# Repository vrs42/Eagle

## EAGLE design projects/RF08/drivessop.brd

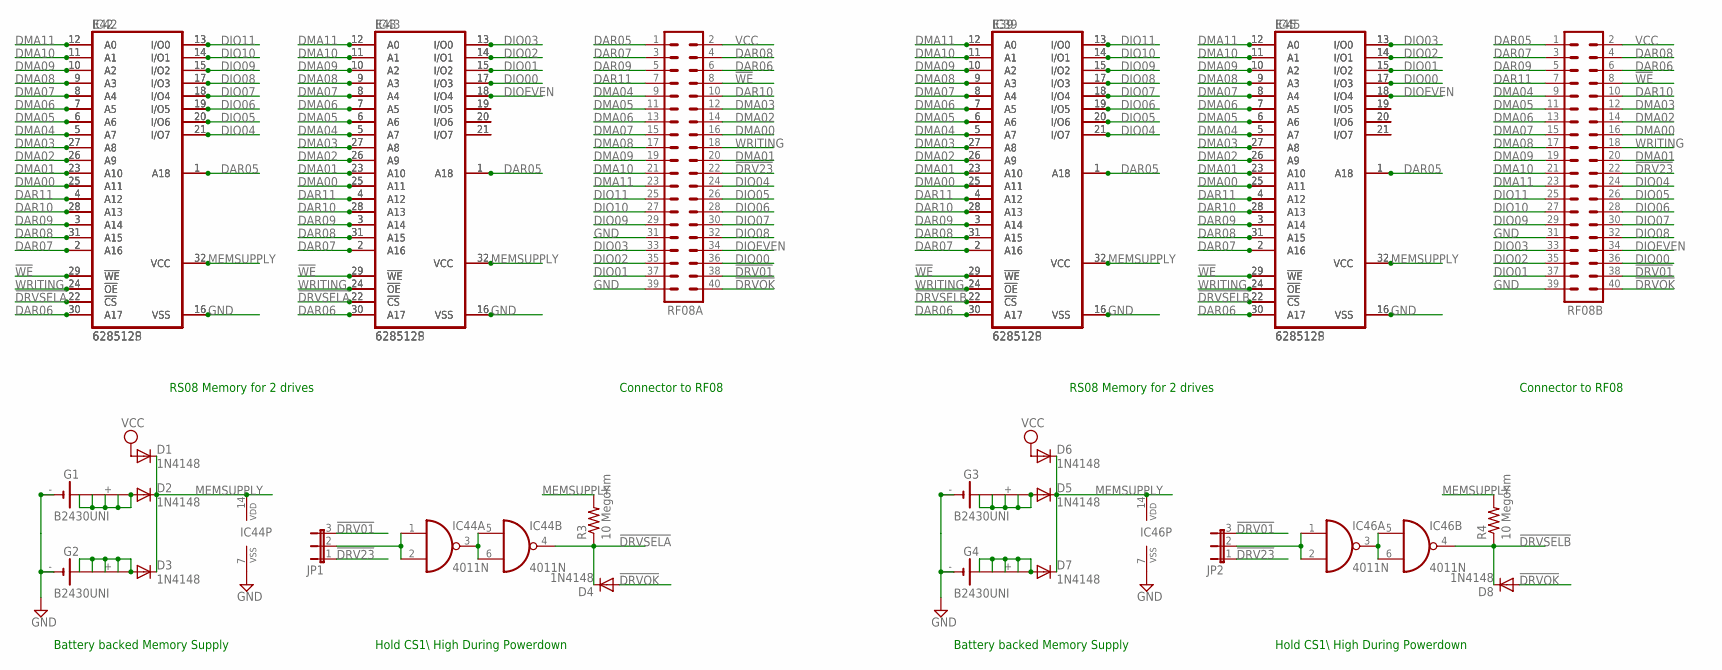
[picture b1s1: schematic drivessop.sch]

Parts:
D1, D2, D3, D4, D5, D6, D7, D8: 1N4148; DO35-10
E39, E42, E43, E45: 628512S; S032L
G1, G2, G3, G4: B2430UNI
IC39, IC42, IC43, IC45: 628512P; DIL32
IC44, IC46: 4011N; DIL14
JP1, JP2: JP2E; JP2
R3, R4: 10 Megohm; 0207/10
RF08A, RF08B: MA20-2

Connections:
!DRV01: JP1.3, JP2.3, RF08A.38, RF08B.38
!DRV23: JP1.1, JP2.1, RF08A.22, RF08B.22
!DRVOK: D4.A, D8.A, RF08A.40, RF08B.40
!DRVSELA: D4.C, E42.22 (!CS), E43.22 (!CS), IC42.22 (!CS), IC43.22 (!CS), IC44.4 (O), R3.1
!DRVSELB: D8.C, E39.22 (!CS), E45.22 (!CS), IC39.22 (!CS), IC45.22 (!CS), IC46.4 (O), R4.1
!WE: E39.29 (!WE), E42.29 (!WE), E43.29 (!WE), E45.29 (!WE), IC39.29 (!WE), IC42.29 (!WE), IC43.29 (!WE), IC45.29 (!WE), RF08A.8, RF08B.8
DAR05: E39.1 (A18), E42.1 (A18), E43.1 (A18), E45.1 (A18), IC39.1 (A18), IC42.1 (A18), IC43.1 (A18), IC45.1 (A18), RF08A.1, RF08B.1
DAR06: E39.30 (A17), E42.30 (A17), E43.30 (A17), E45.30 (A17), IC39.30 (A17), IC42.30 (A17), IC43.30 (A17), IC45.30 (A17), RF08A.6, RF08B.6
DAR07: E39.2 (A16), E42.2 (A16), E43.2 (A16), E45.2 (A16), IC39.2 (A16), IC42.2 (A16), IC43.2 (A16), IC45.2 (A16), RF08A.3, RF08B.3
DAR08: E39.31 (A15), E42.31 (A15), E43.31 (A15), E45.31 (A15), IC39.31 (A15), IC42.31 (A15), IC43.31 (A15), IC45.31 (A15), RF08A.4, RF08B.4
DAR09: E39.3 (A14), E42.3 (A14), E43.3 (A14), E45.3 (A14), IC39.3 (A14), IC42.3 (A14), IC43.3 (A14), IC45.3 (A14), RF08A.5, RF08B.5
DAR10: E39.28 (A13), E42.28 (A13), E43.28 (A13), E45.28 (A13), IC39.28 (A13), IC42.28 (A13), IC43.28 (A13), IC45.28 (A13), RF08A.10, RF08B.10
DAR11: E39.4 (A12), E42.4 (A12), E43.4 (A12), E45.4 (A12), IC39.4 (A12), IC42.4 (A12), IC43.4 (A12), IC45.4 (A12), RF08A.7, RF08B.7
DIO00: E43.17 (I/O3), E45.17 (I/O3), IC43.17 (I/O3), IC45.17 (I/O3), RF08A.36, RF08B.36
DIO01: E43.15 (I/O2), E45.15 (I/O2), IC43.15 (I/O2), IC45.15 (I/O2), RF08A.37, RF08B.37
DIO02: E43.14 (I/O1), E45.14 (I/O1), IC43.14 (I/O1), IC45.14 (I/O1), RF08A.35, RF08B.35
DIO03: E43.13 (I/O0), E45.13 (I/O0), IC43.13 (I/O0), IC45.13 (I/O0), RF08A.33, RF08B.33
DIO04: E39.21 (I/O7), E42.21 (I/O7), IC39.21 (I/O7), IC42.21 (I/O7), RF08A.24, RF08B.24
DIO05: E39.20 (I/O6), E42.20 (I/O6), IC39.20 (I/O6), IC42.20 (I/O6), RF08A.26, RF08B.26
DIO06: E39.19 (I/O5), E42.19 (I/O5), IC39.19 (I/O5), IC42.19 (I/O5), RF08A.28, RF08B.28
DIO07: E39.18 (I/O4), E42.18 (I/O4), IC39.18 (I/O4), IC42.18 (I/O4), RF08A.30, RF08B.30
DIO08: E39.17 (I/O3), E42.17 (I/O3), IC39.17 (I/O3), IC42.17 (I/O3), RF08A.32, RF08B.32
DIO09: E39.15 (I/O2), E42.15 (I/O2), IC39.15 (I/O2), IC42.15 (I/O2), RF08A.29, RF08B.29
DIO10: E39.14 (I/O1), E42.14 (I/O1), IC39.14 (I/O1), IC42.14 (I/O1), RF08A.27, RF08B.27
DIO11: E39.13 (I/O0), E42.13 (I/O0), IC39.13 (I/O0), IC42.13 (I/O0), RF08A.25, RF08B.25
DIOEVEN: E43.18 (I/O4), E45.18 (I/O4), IC43.18 (I/O4), IC45.18 (I/O4), RF08A.34, RF08B.34
DMA00: E39.25 (A11), E42.25 (A11), E43.25 (A11), E45.25 (A11), IC39.25 (A11), IC42.25 (A11), IC43.25 (A11), IC45.25 (A11), RF08A.16, RF08B.16
DMA01: E39.23 (A10), E42.23 (A10), E43.23 (A10), E45.23 (A10), IC39.23 (A10), IC42.23 (A10), IC43.23 (A10), IC45.23 (A10), RF08A.20, RF08B.20
DMA02: E39.26 (A9), E42.26 (A9), E43.26 (A9), E45.26 (A9), IC39.26 (A9), IC42.26 (A9), IC43.26 (A9), IC45.26 (A9), RF08A.14, RF08B.14
DMA03: E39.27 (A8), E42.27 (A8), E43.27 (A8), E45.27 (A8), IC39.27 (A8), IC42.27 (A8), IC43.27 (A8), IC45.27 (A8), RF08A.12, RF08B.12
DMA04: E39.5 (A7), E42.5 (A7), E43.5 (A7), E45.5 (A7), IC39.5 (A7), IC42.5 (A7), IC43.5 (A7), IC45.5 (A7), RF08A.9, RF08B.9
DMA05: E39.6 (A6), E42.6 (A6), E43.6 (A6), E45.6 (A6), IC39.6 (A6), IC42.6 (A6), IC43.6 (A6), IC45.6 (A6), RF08A.11, RF08B.11
DMA06: E39.7 (A5), E42.7 (A5), E43.7 (A5), E45.7 (A5), IC39.7 (A5), IC42.7 (A5), IC43.7 (A5), IC45.7 (A5), RF08A.13, RF08B.13
DMA07: E39.8 (A4), E42.8 (A4), E43.8 (A4), E45.8 (A4), IC39.8 (A4), IC42.8 (A4), IC43.8 (A4), IC45.8 (A4), RF08A.15, RF08B.15
DMA08: E39.9 (A3), E42.9 (A3), E43.9 (A3), E45.9 (A3), IC39.9 (A3), IC42.9 (A3), IC43.9 (A3), IC45.9 (A3), RF08A.17, RF08B.17
DMA09: E39.10 (A2), E42.10 (A2), E43.10 (A2), E45.10 (A2), IC39.10 (A2), IC42.10 (A2), IC43.10 (A2), IC45.10 (A2), RF08A.19, RF08B.19
DMA10: E39.11 (A1), E42.11 (A1), E43.11 (A1), E45.11 (A1), IC39.11 (A1), IC42.11 (A1), IC43.11 (A1), IC45.11 (A1), RF08A.21, RF08B.21
DMA11: E39.12 (A0), E42.12 (A0), E43.12 (A0), E45.12 (A0), IC39.12 (A0), IC42.12 (A0), IC43.12 (A0), IC45.12 (A0), RF08A.23, RF08B.23
GND: E39.16 (VSS), E42.16 (VSS), E43.16 (VSS), E45.16 (VSS), G1.-, G1.-@1 (-), G2.-, G2.-@1 (-), G3.-, G3.-@1 (-), G4.-, G4.-@1 (-), IC39.16 (VSS), IC42.16 (VSS), IC43.16 (VSS), IC44.7 (VSS), IC45.16 (VSS), IC46.7 (VSS), RF08A.31, RF08A.39, RF08B.31, RF08B.39
MEMSUPPLY: D1.C, D2.C, D3.C, D5.C, D6.C, D7.C, E39.32 (VCC), E42.32 (VCC), E43.32 (VCC), E45.32 (VCC), IC39.32 (VCC), IC42.32 (VCC), IC43.32 (VCC), IC44.14 (VDD), IC45.32 (VCC), IC46.14 (VDD), R3.2, R4.2
unnamed: E43.19 (I/O5), IC43.19 (I/O5)
unnamed: E43.20 (I/O6), IC43.20 (I/O6)
unnamed: E43.21 (I/O7), IC43.21 (I/O7)
unnamed: E45.19 (I/O5), IC45.19 (I/O5)
unnamed: E45.20 (I/O6), IC45.20 (I/O6)
unnamed: E45.21 (I/O7), IC45.21 (I/O7)
unnamed: IC44.3 (O), IC44.5 (I0), IC44.6 (I1)
unnamed: IC44.1 (I0), IC44.2 (I1), JP1.2
unnamed: D7.A, G4.+, G4.+@1 (+), G4.+@2 (+), G4.+@3 (+), G4.+@4 (+)
unnamed: IC46.3 (O), IC46.5 (I0), IC46.6 (I1)
unnamed: IC46.1 (I0), IC46.2 (I1), JP2.2
unnamed: D5.A, G3.+, G3.+@1 (+), G3.+@2 (+), G3.+@3 (+), G3.+@4 (+)
unnamed: D3.A, G2.+, G2.+@1 (+), G2.+@2 (+), G2.+@3 (+), G2.+@4 (+)
unnamed: D2.A, G1.+, G1.+@1 (+), G1.+@2 (+), G1.+@3 (+), G1.+@4 (+)
VCC: D1.A, D6.A, RF08A.2, RF08B.2
WRITING: E39.24 (!OE), E42.24 (!OE), E43.24 (!OE), E45.24 (!OE), IC39.24 (!OE), IC42.24 (!OE), IC43.24 (!OE), IC45.24 (!OE), RF08A.18, RF08B.18

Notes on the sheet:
Hold CS1\\ High During Powerdown
Battery backed Memory Supply
RS08 Memory for 2 drives
Connector to RF08

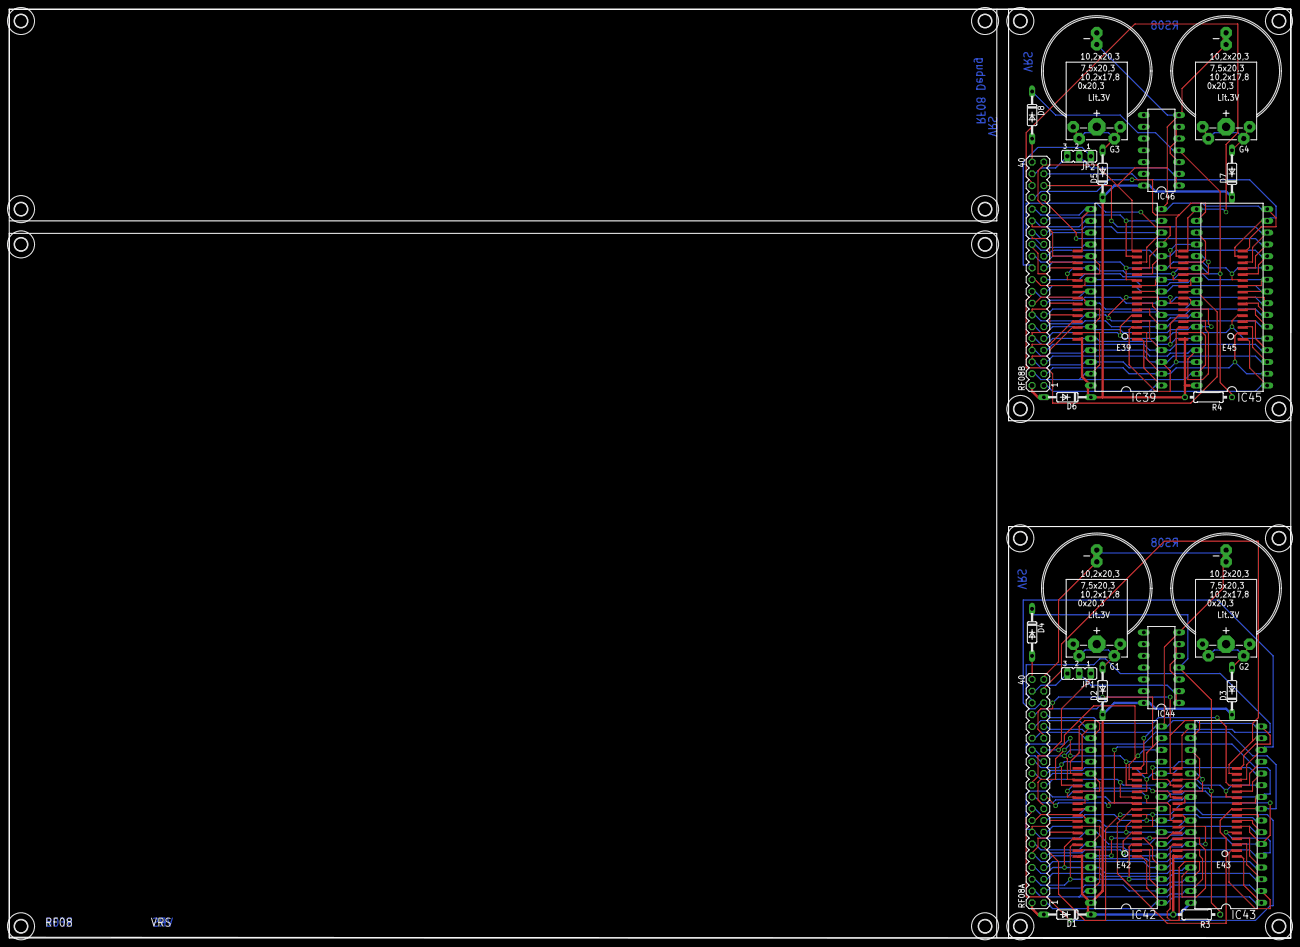
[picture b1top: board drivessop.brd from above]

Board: 2 copper layers, 276.9 x 200.7 mm, 45 parts (0 on the bottom side), 56 nets.

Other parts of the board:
U$1, U$2, U$3, U$4, U$5, U$6, U$7, U$8, U$9, U$10, U$11, U$12, U$13, U$14, U$16, U$17: 2,8
U$18: SIERRA-PROTO

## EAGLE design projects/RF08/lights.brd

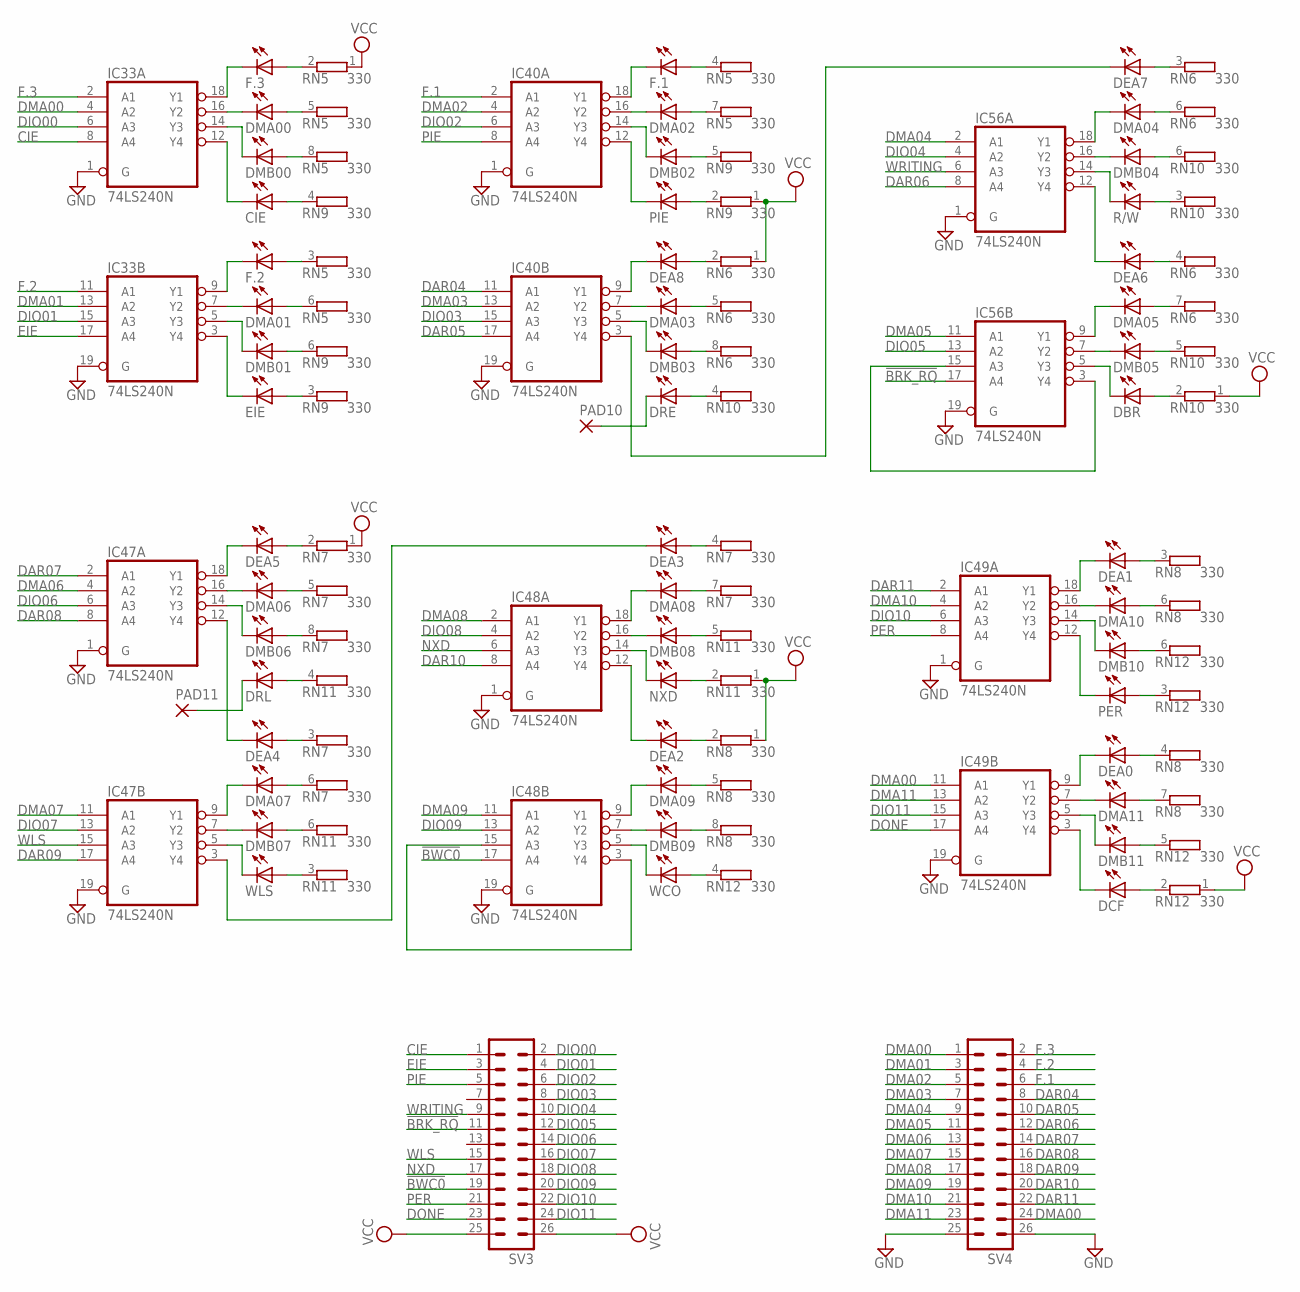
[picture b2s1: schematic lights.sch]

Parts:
CIE: LED5MM
DBR: LED5MM
DCF: LED5MM
DEA0, DEA1, DEA2, DEA3, DEA4, DEA5, DEA6, DEA7, DEA8: LED5MM
DMA00, DMA01, DMA02, DMA03, DMA04, DMA05, DMA06, DMA07, DMA08, DMA09, DMA10, DMA11: LED5MM
DMB00, DMB01, DMB02, DMB03, DMB04, DMB05, DMB06, DMB07, DMB08, DMB09, DMB10, DMB11: LED5MM
DRE: LED5MM
DRL: LED5MM
EIE: LED5MM
F.1, F.2, F.3: LED5MM
IC33, IC40, IC47, IC48, IC49, IC56: 74LS240N; DIL20
NXD: LED5MM
PAD10, PAD11: 1,6/0,8
PER: LED5MM
PIE: LED5MM
R/W: LED5MM
RN5, RN6, RN7, RN8: 330; SIL8
RN9, RN10, RN11, RN12: 330; SIL6
SV3, SV4: MA13-2
WCO: LED5MM
WLS: LED5MM

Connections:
!BRK_RQ: IC56.17 (A4), SV3.11
!BWC0: IC48.17 (A4), SV3.19
CIE: IC33.8 (A4), SV3.1
DAR04: IC40.11 (A1), SV4.8
DAR05: IC40.17 (A4), SV4.10
DAR06: IC56.8 (A4), SV4.12
DAR07: IC47.2 (A1), SV4.14
DAR08: IC47.8 (A4), SV4.16
DAR09: IC47.17 (A4), SV4.18
DAR10: IC48.8 (A4), SV4.20
DAR11: IC49.2 (A1), SV4.22
DIO00: IC33.6 (A3), SV3.2
DIO01: IC33.15 (A3), SV3.4
DIO02: IC40.6 (A3), SV3.6
DIO03: IC40.15 (A3), SV3.8
DIO04: IC56.4 (A2), SV3.10
DIO05: IC56.13 (A2), SV3.12
DIO06: IC47.6 (A3), SV3.14
DIO07: IC47.13 (A2), SV3.16
DIO08: IC48.4 (A2), SV3.18
DIO09: IC48.13 (A2), SV3.20
DIO10: IC49.6 (A3), SV3.22
DIO11: IC49.15 (A3), SV3.24
DMA00: IC33.4 (A2), IC49.11 (A1), SV4.1, SV4.24
DMA01: IC33.13 (A2), SV4.3
DMA02: IC40.4 (A2), SV4.5
DMA03: IC40.13 (A2), SV4.7
DMA04: IC56.2 (A1), SV4.9
DMA05: IC56.11 (A1), SV4.11
DMA06: IC47.4 (A2), SV4.13
DMA07: IC47.11 (A1), SV4.15
DMA08: IC48.2 (A1), SV4.17
DMA09: IC48.11 (A1), SV4.19
DMA10: IC49.4 (A2), SV4.21
DMA11: IC49.13 (A2), SV4.23
DONE: IC49.17 (A4), SV3.23
EIE: IC33.17 (A4), SV3.3
F.1: IC40.2 (A1), SV4.6
F.2: IC33.11 (A1), SV4.4
F.3: IC33.2 (A1), SV4.2
GND: IC33.1 (G), IC33.10 (GND), IC33.19 (G), IC40.1 (G), IC40.10 (GND), IC40.19 (G), IC47.1 (G), IC47.10 (GND), IC47.19 (G), IC48.1 (G), IC48.10 (GND), IC48.19 (G), IC49.1 (G), IC49.10 (GND), IC49.19 (G), IC56.1 (G), IC56.10 (GND), IC56.19 (G), SV4.25, SV4.26
unnamed: F.3.A, RN5.2
unnamed: F.2.A, RN5.3 (2)
unnamed: F.1.A, RN5.4 (2)
unnamed: DEA8.A, RN6.2
unnamed: DEA2.A, RN8.2
unnamed: DEA1.A, RN8.3 (2)
unnamed: DEA5.A, RN7.2
unnamed: DEA4.A, RN7.3 (2)
unnamed: DEA3.A, RN7.4 (2)
unnamed: DEA0.A, RN8.4 (2)
unnamed: DMA09.A, RN8.5 (2)
unnamed: DMA10.A, RN8.6 (2)
unnamed: DMA00.A, RN5.5 (2)
unnamed: DMA01.A, RN5.6 (2)
unnamed: DMA02.A, RN5.7 (2)
unnamed: DEA7.A, RN6.3 (2)
unnamed: DEA6.A, RN6.4 (2)
unnamed: DMA03.A, RN6.5 (2)
unnamed: DMA07.A, RN7.6 (2)
unnamed: DMA06.A, RN7.5 (2)
unnamed: DMA08.A, RN7.7 (2)
unnamed: DMA11.A, RN8.7 (2)
unnamed: DMB09.A, RN8.8 (2)
unnamed: DMB10.A, RN12.6 (2)
unnamed: PIE.A, RN9.2
unnamed: EIE.A, RN9.3 (2)
unnamed: CIE.A, RN9.4 (2)
unnamed: DMA04.A, RN6.6 (2)
unnamed: DMA05.A, RN6.7 (2)
unnamed: DMB03.A, RN6.8 (2)
unnamed: DMB06.A, RN7.8 (2)
unnamed: DMB07.A, RN11.6 (2)
unnamed: DMB08.A, RN11.5 (2)
unnamed: DMB11.A, RN12.5 (2)
unnamed: RN12.4 (2), WCO.A
unnamed: PER.A, RN12.3 (2)
unnamed: DMB02.A, RN9.5 (2)
unnamed: DMB01.A, RN9.6 (2)
unnamed: DMB00.A, RN5.8 (2)
unnamed: DRE.A, RN10.4 (2)
unnamed: R/W.A, RN10.3 (2)
unnamed: DBR.A, RN10.2
unnamed: DRL.A, RN11.4 (2)
unnamed: RN11.3 (2), WLS.A
unnamed: NXD.A, RN11.2
unnamed: DCF.A, RN12.2
unnamed: DMA09.K (C), IC48.9 (Y1)
unnamed: DMB09.K (C), IC48.7 (Y2)
unnamed: F.3.K (C), IC33.18 (Y1)
unnamed: DMA00.K (C), IC33.16 (Y2)
unnamed: CIE.K (C), IC33.12 (Y4)
unnamed: DMB00.K (C), IC33.14 (Y3)
unnamed: DMA01.K (C), IC33.7 (Y2)
unnamed: F.2.K (C), IC33.9 (Y1)
unnamed: DMB01.K (C), IC33.5 (Y3)
unnamed: EIE.K (C), IC33.3 (Y4)
unnamed: F.1.K (C), IC40.18 (Y1)
unnamed: DMA02.K (C), IC40.16 (Y2)
unnamed: DMB02.K (C), IC40.14 (Y3)
unnamed: IC40.12 (Y4), PIE.K (C)
unnamed: DMB03.K (C), IC40.5 (Y3)
unnamed: DMA03.K (C), IC40.7 (Y2)
unnamed: DEA8.K (C), IC40.9 (Y1)
unnamed: DEA7.K (C), IC40.3 (Y4)
unnamed: DMA04.K (C), IC56.18 (Y1)
unnamed: DMB04.K (C), IC56.16 (Y2)
unnamed: IC56.14 (Y3), R/W.K (C)
unnamed: DMB05.K (C), IC56.7 (Y2)
unnamed: DEA6.K (C), IC56.12 (Y4)
unnamed: DBR.K (C), IC56.5 (Y3)
unnamed: DMA06.K (C), IC47.16 (Y2)
unnamed: DEA4.K (C), IC47.12 (Y4)
unnamed: DMB07.K (C), IC47.7 (Y2)
unnamed: DEA5.K (C), IC47.18 (Y1)
unnamed: DMA07.K (C), IC47.9 (Y1)
unnamed: IC47.5 (Y3), WLS.K (C)
unnamed: DMB06.K (C), IC47.14 (Y3)
unnamed: DEA3.K (C), IC47.3 (Y4)
unnamed: DMA08.K (C), IC48.18 (Y1)
unnamed: DMB08.K (C), IC48.16 (Y2)
unnamed: IC48.14 (Y3), NXD.K (C)
unnamed: IC48.5 (Y3), WCO.K (C)
unnamed: IC49.12 (Y4), PER.K (C)
unnamed: DMB10.K (C), IC49.14 (Y3)
unnamed: DEA2.K (C), IC48.12 (Y4)
unnamed: DMA10.K (C), IC49.16 (Y2)
unnamed: DEA1.K (C), IC49.18 (Y1)
unnamed: IC48.3 (Y4), IC48.15 (A3)
unnamed: DMA11.K (C), IC49.7 (Y2)
unnamed: DEA0.K (C), IC49.9 (Y1)
unnamed: DMB11.K (C), IC49.5 (Y3)
unnamed: DCF.K (C), IC49.3 (Y4)
unnamed: DRE.K (C), PAD10.1
unnamed: DRL.K (C), PAD11.1
unnamed: DMA05.K (C), IC56.9 (Y1)
unnamed: DMB04.A, RN10.6 (2)
unnamed: DMB05.A, RN10.5 (2)
unnamed: IC56.3 (Y4), IC56.15 (A3)
NXD: IC48.6 (A3), SV3.17
PER: IC49.8 (A4), SV3.21
PIE: IC40.8 (A4), SV3.5
VCC: IC33.20 (VCC), IC40.20 (VCC), IC47.20 (VCC), IC48.20 (VCC), IC49.20 (VCC), IC56.20 (VCC), RN5.1, RN6.1, RN7.1, RN8.1, RN9.1, RN10.1, RN11.1, RN12.1, SV3.25, SV3.26
WLS: IC47.15 (A3), SV3.15
WRITING: IC56.6 (A3), SV3.9

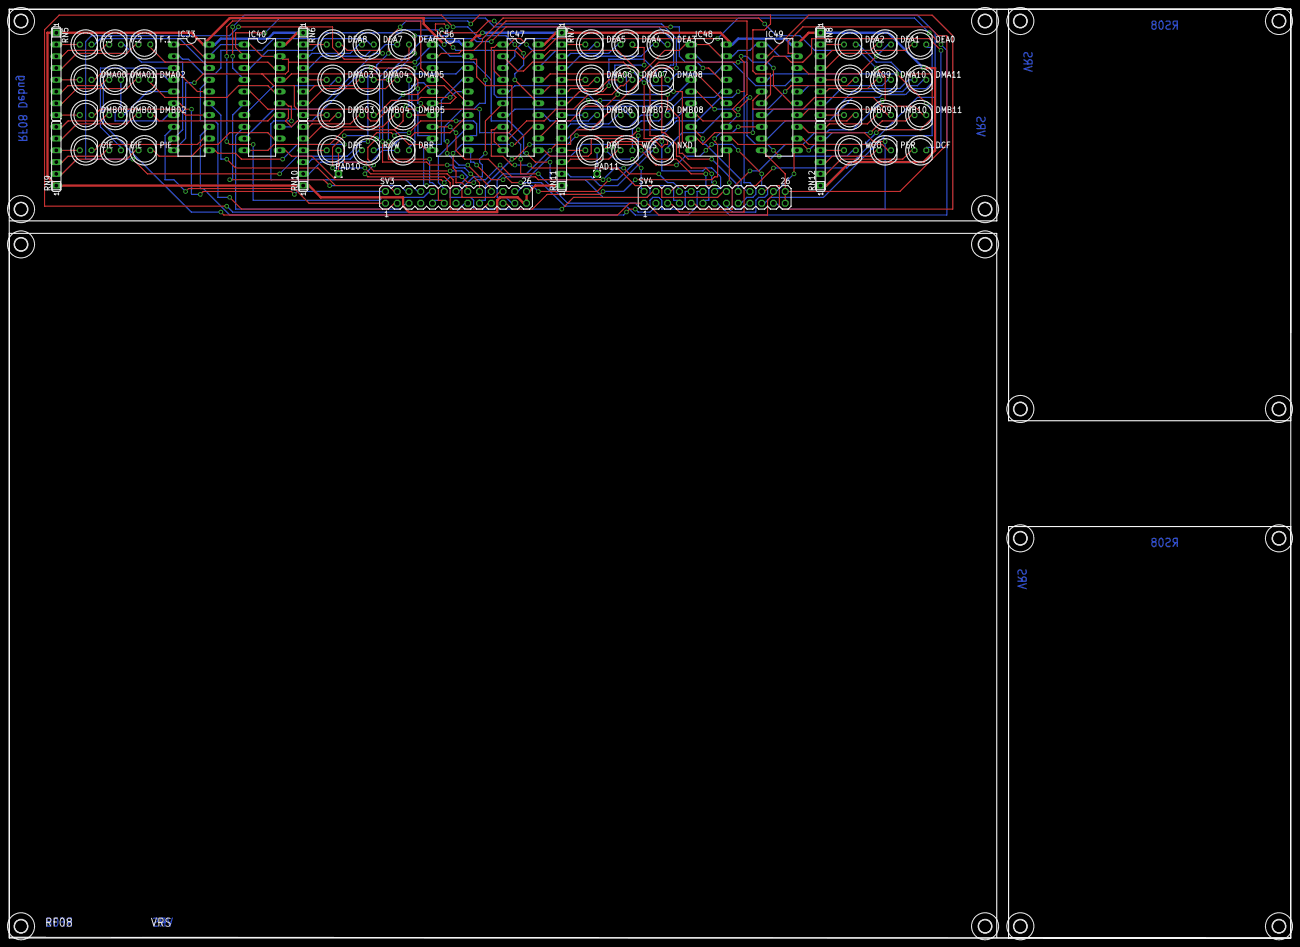
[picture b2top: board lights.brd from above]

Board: 2 copper layers, 276.9 x 200.7 mm, 83 parts (0 on the bottom side), 145 nets.

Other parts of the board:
U$1, U$2, U$3, U$4, U$5, U$6, U$7, U$8, U$9, U$10, U$11, U$12, U$13, U$14, U$16, U$17: 2,8
U$18: SIERRA-PROTO

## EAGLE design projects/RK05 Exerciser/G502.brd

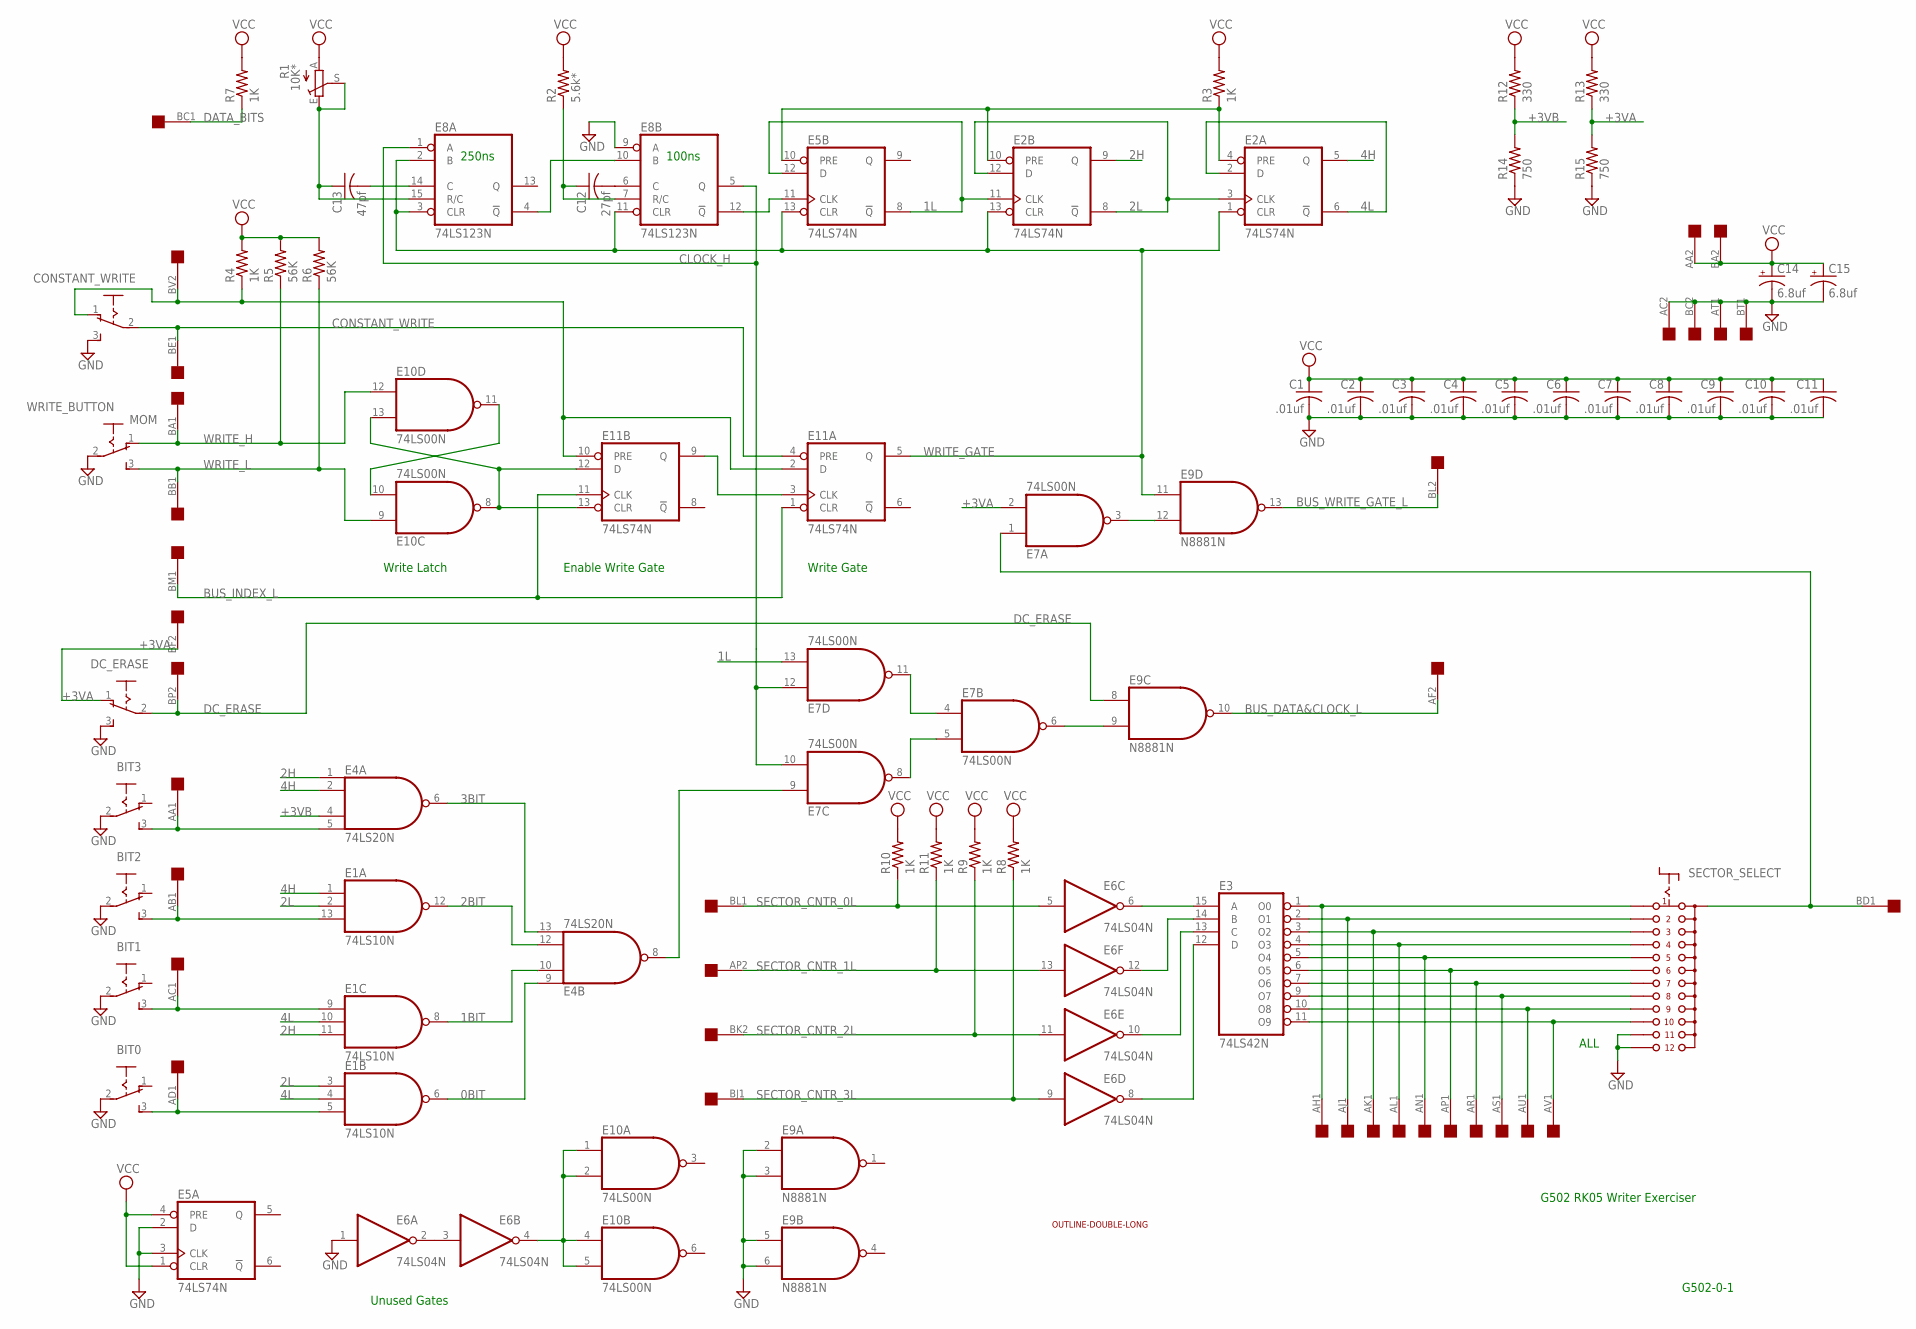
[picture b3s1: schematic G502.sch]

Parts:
AB04: DOUBLE; EDGE-CON4
BIT0, BIT1, BIT2, BIT3: 255SB
C1, C2, C3, C4, C5, C6, C7, C8, C9, C10, C11: .01uf; C075-032X103
C12: 27pf; C075-032X103
C13: 47pf; C075-032X103
C14, C15: 6.8uf; E25-9
CONSTANT_WRITE: 255SB
DC_ERASE: 255SB
E1: 74LS10N; DIL14
E2, E5, E11: 74LS74N; DIL14
E3: 74LS42N; DIL16
E4: 74LS20N; DIL14
E6: 74LS04N; DIL14
E7, E10: 74LS00N; DIL14
E8: 74LS123N; DIL16
E9: N8881N; DIL14
R1: 10K*; SP19L
R2: 5.6k*; 0207/10
R3, R4, R7, R8, R9, R10, R11: 1K; 0207/10
R5, R6: 56K; 0207/10
R12, R13: 330; 0207/10
R14, R15: 750; 0207/10
SECTOR_SELECT: CK101X12
U$2: OUTLINE-DOUBLE-LONG; DOUBLE-LONG
WRITE_BUTTON: MOM; 255SB

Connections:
0BIT: E1.6 (O), E4.9 (I0)
1.44MHZ: E5.11 (CLK), E8.12 (!Q)
1BIT: E1.8 (O), E4.10 (I1)
1L: E2.11 (CLK), E5.8 (!Q), E5.12 (D), E7.13 (I1)
2.88MHZ: E8.4 (!Q), E8.10 (B)
2BIT: E1.12 (O), E4.12 (I2)
2H: E1.11 (I2), E2.9 (Q), E4.1 (I0)
2L: E1.2 (I1), E1.3 (I0), E2.3 (CLK), E2.8 (!Q), E2.12 (D)
3BIT: E4.6 (O), E4.13 (I3)
4H: E1.1 (I0), E2.5 (Q), E4.2 (I1)
4L: E1.4 (I1), E1.10 (I1), E2.2 (D), E2.6 (!Q)
+3VA: AB04.BF2, DC_ERASE.1 (O), E7.2 (I1), R13.1, R15.2
+3VB: E4.4 (I2), R12.1, R14.2
BUS_DATA&CLOCK_L: AB04.AF2, E9.10 (O)
BUS_INDEX_L: AB04.BM1, E11.1 (CLR), E11.11 (CLK)
BUS_WRITE_GATE_L: AB04.BL2, E9.13 (O)
CLOCK_H: E7.10 (I1), E7.12 (I0), E8.1 (A), E8.5 (Q)
CONSTANT_WRITE: AB04.BE1, CONSTANT_WRITE.2, E11.4 (PRE)
DATA_BITS: AB04.BC1, R7.1
DC_ERASE: AB04.BP2, DC_ERASE.2, E9.8 (I0)
GND: AB04.AC2, AB04.AT1, AB04.BC2, AB04.BT1, BIT0.2, BIT1.2, BIT2.2, BIT3.2, C1.2, C2.2, C3.2, C4.2, C5.2, C6.2, C7.2, C8.2, C9.2, C10.2, C11.2, C14.-, C15.-, CONSTANT_WRITE.3 (S), DC_ERASE.3 (S), E1.7 (GND), E2.7 (GND), E3.8 (GND), E4.7 (GND), E5.2 (D), E5.3 (CLK), E5.7 (GND), E6.1 (I), E6.7 (GND), E7.7 (GND), E8.8 (GND), E8.9 (A), E9.2 (I0), E9.3 (I1), E9.5 (I0), E9.6 (I1), E9.7 (GND), E10.7 (GND), E11.7 (GND), R14.1, R15.1, SECTOR_SELECT.11, SECTOR_SELECT.12, WRITE_BUTTON.2
unnamed: AB04.BV2, CONSTANT_WRITE.1 (O), E11.2 (D), E11.10 (PRE), R4.1
unnamed: E7.6 (O), E9.9 (I1)
unnamed: E10.8 (O), E10.13 (I1), E11.12 (D), E11.13 (CLR)
unnamed: E10.10 (I1), E10.11 (O)
unnamed: E2.4 (PRE), E2.10 (PRE), E5.10 (PRE), R3.1
unnamed: E7.4 (I0), E7.11 (O)
unnamed: E7.5 (I1), E7.8 (O)
unnamed: E11.3 (CLK), E11.9 (Q)
unnamed: E4.8 (O), E7.9 (I0)
unnamed: AB04.AC1, BIT1.3 (S), E1.9 (I0)
unnamed: C13.2, E8.14 (C)
unnamed: C12.2, E8.6 (C)
unnamed: C13.1, E8.15 (R/C), R1.E, R1.S
unnamed: C12.1, E8.7 (R/C), R2.1
unnamed: E7.3 (O), E9.12 (I1)
unnamed: AB04.AA1, BIT3.3 (S), E4.5 (I3)
unnamed: AB04.AB1, BIT2.3 (S), E1.13 (I2)
unnamed: AB04.AD1, BIT0.3 (S), E1.5 (I2)
unnamed: AB04.AH1, E3.1 (O0), SECTOR_SELECT.1
unnamed: AB04.AJ1, E3.2 (O1), SECTOR_SELECT.2
unnamed: AB04.AK1, E3.3 (O2), SECTOR_SELECT.3
unnamed: AB04.AL1, E3.4 (O3), SECTOR_SELECT.4
unnamed: AB04.AN1, E3.5 (O4), SECTOR_SELECT.5
unnamed: AB04.AP1, E3.6 (O5), SECTOR_SELECT.6
unnamed: AB04.AR1, E3.7 (O6), SECTOR_SELECT.7
unnamed: AB04.AS1, E3.9 (O7), SECTOR_SELECT.8
unnamed: AB04.AU1, E3.10 (O8), SECTOR_SELECT.9
unnamed: AB04.AV1, E3.11 (O9), SECTOR_SELECT.10
unnamed: E3.15 (A), E6.6 (O)
unnamed: E3.14 (B), E6.12 (O)
unnamed: E3.13 (C), E6.10 (O)
unnamed: E3.12 (D), E6.8 (O)
unnamed: E6.2 (O), E6.3 (I)
unnamed: E6.4 (O), E10.1 (I0), E10.2 (I1), E10.4 (I0), E10.5 (I1)
SECTOR_CNTR_0L: AB04.BL1, E6.5 (I), R10.1
SECTOR_CNTR_1L: AB04.AP2, E6.13 (I), R11.1
SECTOR_CNTR_2L: AB04.BK2, E6.11 (I), R9.1
SECTOR_CNTR_3L: AB04.BJ1, E6.9 (I), R8.1
SECTOR_SELECT_L: AB04.BD1, E7.1 (I0), SECTOR_SELECT.A
VCC: AB04.AA2, AB04.BA2, C1.1, C2.1, C3.1, C4.1, C5.1, C6.1, C7.1, C8.1, C9.1, C10.1, C11.1, C14.+, C15.+, E1.14 (VCC), E2.14 (VCC), E3.16 (VCC), E4.14 (VCC), E5.1 (CLR), E5.4 (PRE), E5.14 (VCC), E6.14 (VCC), E7.14 (VCC), E8.16 (VCC), E9.14 (VCC), E10.14 (VCC), E11.14 (VCC), R1.A, R2.2, R3.2, R4.2, R5.2, R6.2, R7.2, R8.2, R9.2, R10.2, R11.2, R12.2, R13.2
WRITE_GATE: E2.1 (CLR), E2.13 (CLR), E5.13 (CLR), E8.2 (B), E8.3 (CLR), E8.11 (CLR), E9.11 (I0), E11.5 (Q)
WRITE_H: AB04.BA1, E10.12 (I0), R5.1, WRITE_BUTTON.1 (O)
WRITE_L: AB04.BB1, E10.9 (I0), R6.1, WRITE_BUTTON.3 (S)

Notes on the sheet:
Write Latch
Enable Write Gate
Write Gate
250ns
100ns
ALL
Unused Gates
G502 RK05 Writer Exerciser
G502-0-1

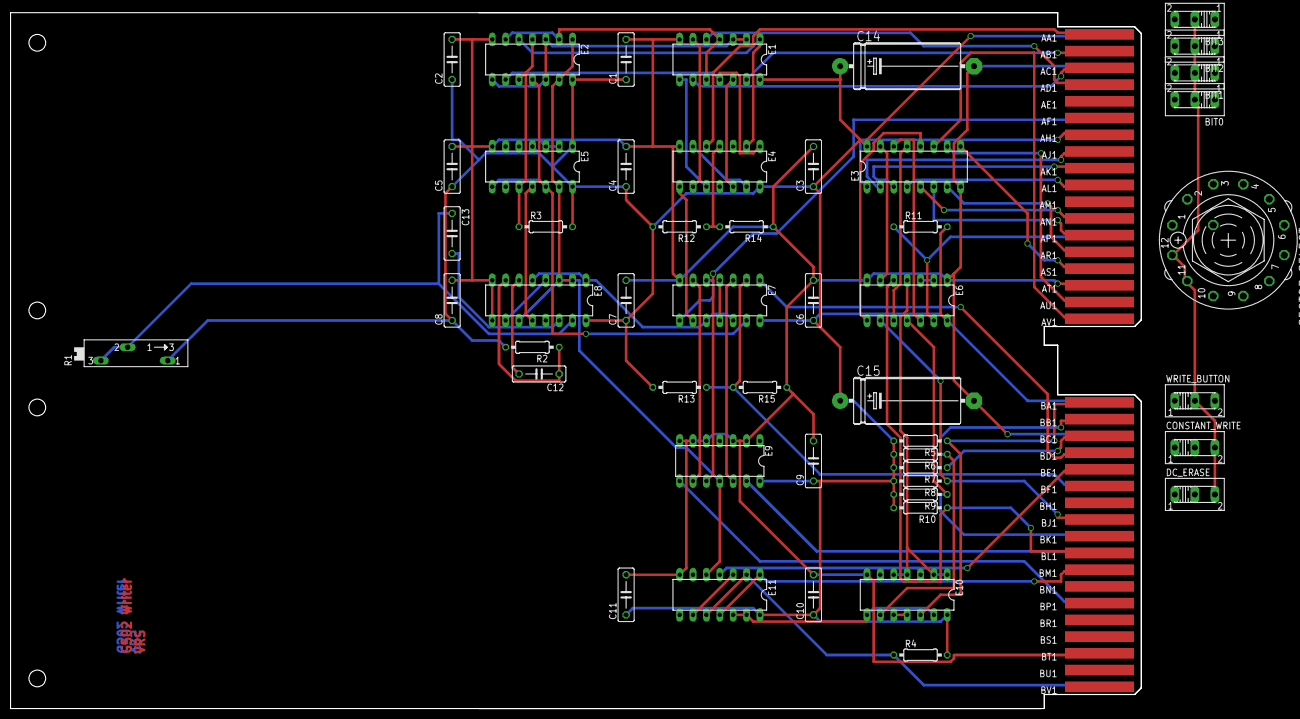
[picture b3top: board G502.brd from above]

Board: 2 copper layers, 214.6 x 132.1 mm, 51 parts (0 on the bottom side), 64 nets.
